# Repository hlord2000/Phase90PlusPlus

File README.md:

# This is a modified and extended Phase90 pedal, intended to fit into a [1590BB enclosure](https://lovemyswitches.com/1590bb-enclosure-bare-aluminum-powder-coat/). Enjoy.

## Interesting features
This pedal uses a software-controlled LFO [(StompLFO, a PIC microcontroller programmed by ElectricDruid)](https://electricdruid.net/product/stomplfo/) to generate a cool bunch of waveforms. The specific waveform is controlled with a potentiometer. An op-amp mixer is included on the output of the pedal, too, so that a musician can alter the mix of wet/dry tone. Finally, the traditional frequency potentiometer is included. This is a true bypass pedal.

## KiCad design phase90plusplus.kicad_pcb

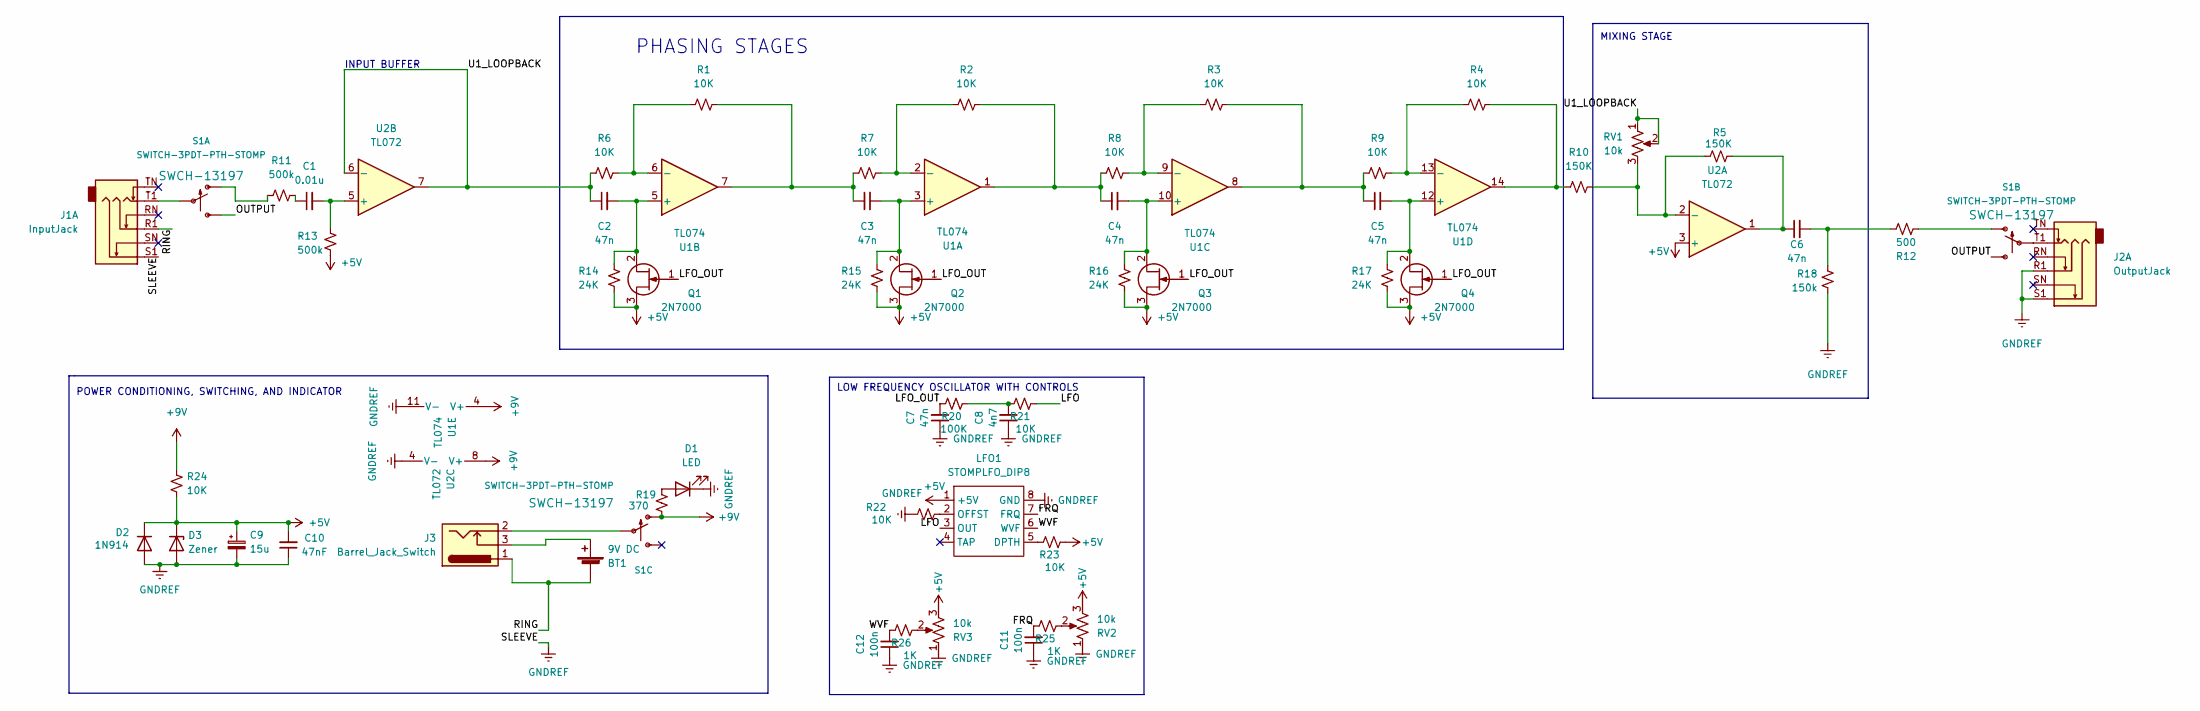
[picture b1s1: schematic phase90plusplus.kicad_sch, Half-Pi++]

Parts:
BT1: 9V DC; JST_EH_S2B-EH_1x02_P2.50mm_Horizontal
C1: 0.01u; C_Disc_D7.5mm_W2.5mm_P5.00mm
C2, C3, C4, C5, C6, C7: 47n; C_Disc_D7.5mm_W2.5mm_P5.00mm
C8: 4n7; C_Disc_D7.5mm_W2.5mm_P5.00mm
C9: 15u; CP_Radial_D4.0mm_P1.50mm
C10: 47nF; C_Disc_D7.5mm_W2.5mm_P5.00mm
C11, C12: 100n; C_Disc_D7.5mm_W2.5mm_P5.00mm
D1: LED; LED_D3.0mm
D2: 1N914; D_DO-35_SOD27_P7.62mm_Horizontal
D3: Zener; D_DO-35_SOD27_P7.62mm_Horizontal
J1: InputJack; Jack_6.35mm_Neutrik_NRJ6HM-1_Horizontal
J2: OutputJack; Jack_6.35mm_Neutrik_NRJ6HM-1_Horizontal
J3: Barrel_Jack_Switch; BarrelJack_Horizontal
LFO1: STOMPLFO_DIP8; DIP-8_W7.62mm_Socket
Q1, Q2, Q3, Q4: 2N7000; TO-92_Inline
R1, R2, R3, R4, R6, R7, R8, R9, R21, R22, R23, R24: 10K; R_Axial_DIN0207_L6.3mm_D2.5mm_P10.16mm_Horizontal
R5, R10: 150K; R_Axial_DIN0207_L6.3mm_D2.5mm_P10.16mm_Horizontal
R11, R13: 500k; R_Axial_DIN0207_L6.3mm_D2.5mm_P10.16mm_Horizontal
R12: 500; R_Axial_DIN0207_L6.3mm_D2.5mm_P10.16mm_Horizontal
R14, R15, R16, R17: 24K; R_Axial_DIN0207_L6.3mm_D2.5mm_P10.16mm_Horizontal
R18: 150k; R_Axial_DIN0207_L6.3mm_D2.5mm_P10.16mm_Horizontal
R19: 370; R_Axial_DIN0207_L6.3mm_D2.5mm_P10.16mm_Horizontal
R20: 100K; R_Axial_DIN0207_L6.3mm_D2.5mm_P10.16mm_Horizontal
R25, R26: 1K; R_Axial_DIN0207_L6.3mm_D2.5mm_P10.16mm_Horizontal
RV1, RV2, RV3: 10k; SolderWire-0.1sqmm_1x03_P3.6mm_D0.4mm_OD1mm_Relief
S1: SWITCH-3PDT-PTH-STOMP; STOMP_SWITCH_3PDT
U1: TL074; DIP-14_W7.62mm
U2: TL072; DIP-8_W7.62mm

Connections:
+5V: C9.1, C10.2, D2.1 (K), D3.1 (K), LFO1.1 (+5V), Q1.3 (D), Q2.3 (D), Q3.3 (D), Q4.3 (D), R13.1, R14.1, R15.1, R16.1, R17.1, R23.1, R24.2, RV2.3, RV3.3, U2.3 (+)
+9V: R19.1, R24.1, S1.P$7 (O), U1.4 (V+), U2.8 (V+)
/FRQ: C11.2, LFO1.7 (FRQ), R25.2
/LFO: LFO1.3 (OUT), R21.1
/LFO_OUT: C7.2, Q1.1 (G), Q2.1 (G), Q3.1 (G), Q4.1 (G), R20.2
/OUTPUT: S1.P$3 (S), S1.P$6 (S)
/RING: BT1.2 (-), J1.R1, J3.1
/U1_LOOPBACK: C2.1, R6.1, RV1.1, RV1.2, U2.6 (-), U2.7
/WVF: C12.2, LFO1.6 (WVF), R26.2
GNDREF: C7.1, C8.1, C9.2, C10.1, C11.1, C12.1, D1.1 (K), D2.2 (A), D3.2 (A), J1.S1, J2.R1, J2.S1, LFO1.8 (GND), R18.1, R22.2, RV2.1, RV3.1, U1.11 (V-), U2.4 (V-)
unnamed: BT1.1 (+), J3.3
unnamed: C1.1, R11.2
unnamed: C1.2, R13.2, U2.5 (+)
unnamed: C2.2, Q1.2 (S), R14.2, U1.5 (+)
unnamed: C3.1, R1.2, R7.1, U1.7
unnamed: C3.2, Q2.2 (S), R15.2, U1.3 (+)
unnamed: C4.1, R2.2, R8.1, U1.1
unnamed: C4.2, Q3.2 (S), R16.2, U1.10 (+)
unnamed: C5.1, R3.2, R9.1, U1.8
unnamed: C5.2, Q4.2 (S), R17.2, U1.12 (+)
unnamed: C6.1, R5.2, U2.1
unnamed: C6.2, R12.2, R18.2
unnamed: C8.2, R20.1, R21.2
unnamed: D1.2 (A), R19.2
unnamed: J1.T1, S1.P$2
unnamed: J2.T1, S1.P$5
unnamed: J3.2, S1.P$8
unnamed: LFO1.2 (OFFST), R22.1
unnamed: LFO1.5 (DPTH), R23.2
unnamed: R1.1, R6.2, U1.6 (-)
unnamed: R2.1, R7.2, U1.2 (-)
unnamed: R3.1, R8.2, U1.9 (-)
unnamed: R4.1, R9.2, U1.13 (-)
unnamed: R4.2, R10.1, U1.14
unnamed: R5.1, R10.2, RV1.3, U2.2 (-)
unnamed: R11.1, S1.P$1 (O)
unnamed: R12.1, S1.P$4 (O)
unnamed: R25.1, RV2.2
unnamed: R26.1, RV3.2

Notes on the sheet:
INPUT BUFFER
POWER CONDITIONING, SWITCHING, AND INDICATOR
LOW FREQUENCY OSCILLATOR WITH CONTROLS
MIXING STAGE
PHASING STAGES

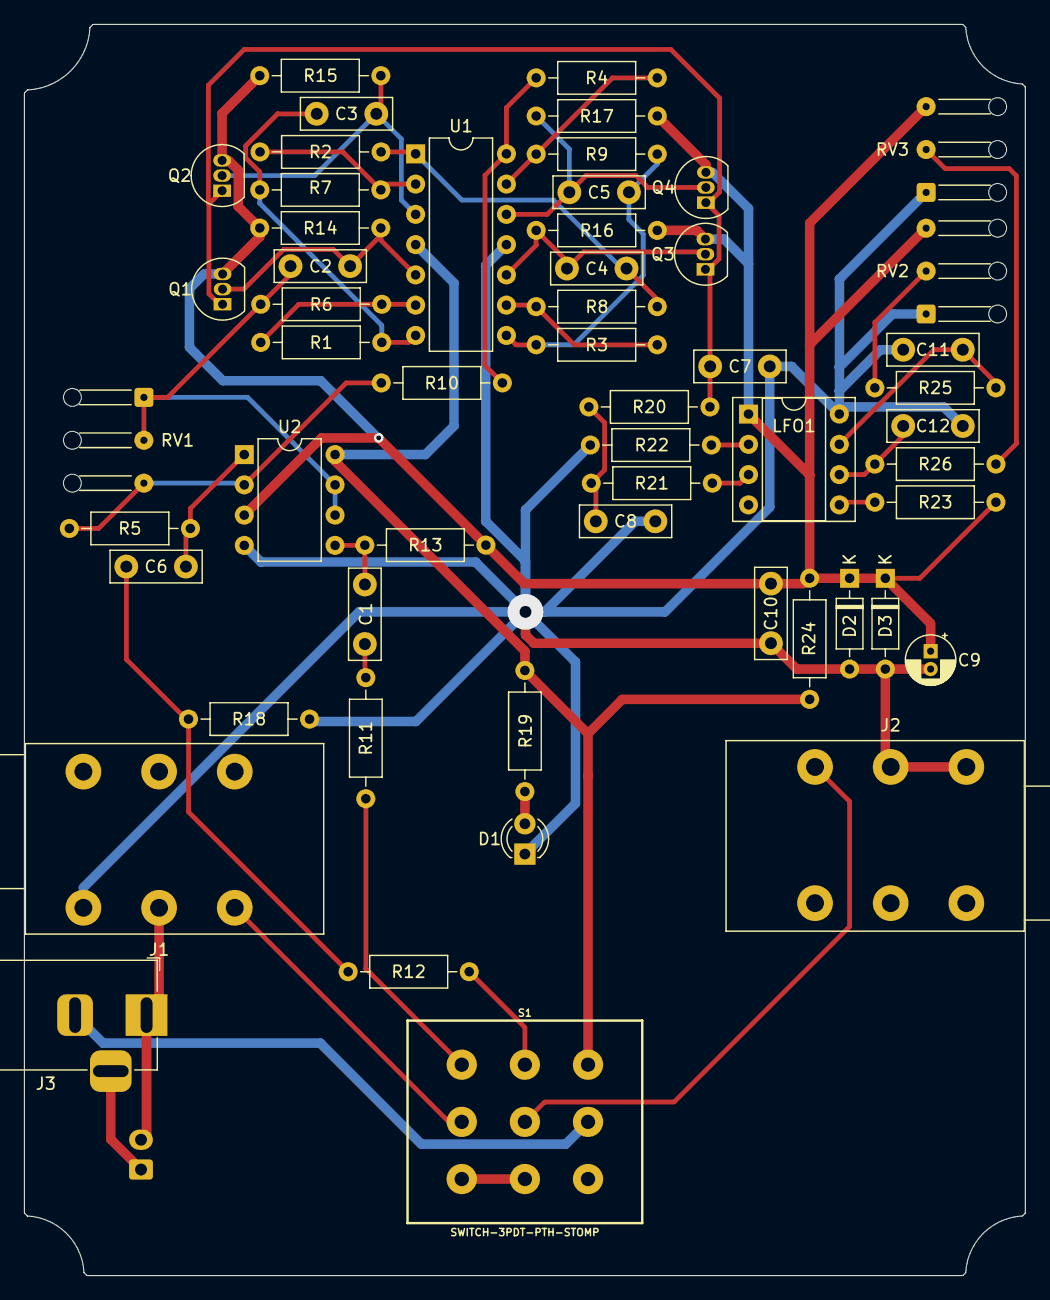
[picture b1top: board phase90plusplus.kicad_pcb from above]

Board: 2 copper layers, 84.0 x 105.0 mm, 56 parts (1 on the bottom side), 39 nets.

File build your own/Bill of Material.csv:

"Source:","C:\Users\Helmut Lord\Documents\Phase90++\phase90plusplus.kicad_sch"
"Date:","5/4/2022 3:37:26 PM"
"Tool:","Eeschema (6.0.1)"
"Generator:","C:\Program Files\KiCad\6.0\bin\scripting\plugins/bom_csv_grouped_by_value_with_fp.py"
"Component Count:","56"
"Ref","Qnty","Value","Cmp name","Footprint","Description","Vendor"
"BT1, ","1","9V DC","Battery_Cell","Connector_JST:JST_EH_S2B-EH_1x02_P2.50mm_Horizontal","Single-cell battery",""
"C1, ","1","0.01u","C_Small","Capacitor_THT:C_Disc_D7.5mm_W2.5mm_P5.00mm","Unpolarized capacitor, small symbol",""
"C2, C3, C4, C5, C6, C7, ","6","47n","C_Small","Capacitor_THT:C_Disc_D7.5mm_W2.5mm_P5.00mm","Unpolarized capacitor, small symbol",""
"C8, ","1","4n7","C_Small","Capacitor_THT:C_Disc_D7.5mm_W2.5mm_P5.00mm","Unpolarized capacitor, small symbol",""
"C9, ","1","15u","C_Polarized_Small","Capacitor_THT:CP_Radial_D4.0mm_P1.50mm","Polarized capacitor, small symbol",""
"C10, ","1","47nF","C_Small","Capacitor_THT:C_Disc_D7.5mm_W2.5mm_P5.00mm","Unpolarized capacitor, small symbol",""
"C11, C12, ","2","100n","C_Small","Capacitor_THT:C_Disc_D7.5mm_W2.5mm_P5.00mm","Unpolarized capacitor, small symbol",""
"D1, ","1","LED","LED","LED_THT:LED_D3.0mm","Light emitting diode",""
"D2, ","1","1N914","1N914","Diode_THT:D_DO-35_SOD27_P7.62mm_Horizontal","100V 0.3A Small Signal Fast Switching Diode, DO-35",""
"D3, ","1","Zener","D_Zener","Diode_THT:D_DO-35_SOD27_P7.62mm_Horizontal","Zener diode",""
"J1, ","1","InputJack","AudioJack3_Dual_Switch_1","Connector_Audio:Jack_6.35mm_Neutrik_NRJ6HM-1_Horizontal","Audio Jack, Dual, 3 Poles (Stereo / TRS), Switched Poles (Normalling)",""
"J2, ","1","OutputJack","AudioJack3_Dual_Switch","Connector_Audio:Jack_6.35mm_Neutrik_NRJ6HM-1_Horizontal","Audio Jack, Dual, 3 Poles (Stereo / TRS), Switched Poles (Normalling)",""
"J3, ","1","Barrel_Jack_Switch","Barrel_Jack_Switch","Connector_BarrelJack:BarrelJack_Horizontal","DC Barrel Jack with an internal switch",""
"LFO1, ","1","STOMPLFO_DIP8","STOMPLFO_DIP8","Package_DIP:DIP-8_W7.62mm_Socket","",""
"Q1, Q2, Q3, Q4, ","4","2N7000","BF245A","Package_TO_SOT_THT:TO-92_Inline","50mA Id, 30V Vgs, N-Channel FET Transistor, TO-92",""
"R1, R2, R3, R4, R6, R7, R8, R9, R21, R22, R23, R24, ","12","10K","R_Small_US","Resistor_THT:R_Axial_DIN0207_L6.3mm_D2.5mm_P10.16mm_Horizontal","Resistor, small US symbol",""
"R5, R10, ","2","150K","R_Small_US","Resistor_THT:R_Axial_DIN0207_L6.3mm_D2.5mm_P10.16mm_Horizontal","Resistor, small US symbol",""
"R11, R13, ","2","500k","R_Small_US","Resistor_THT:R_Axial_DIN0207_L6.3mm_D2.5mm_P10.16mm_Horizontal","Resistor, small US symbol",""
"R12, ","1","500","R_Small_US","Resistor_THT:R_Axial_DIN0207_L6.3mm_D2.5mm_P10.16mm_Horizontal","Resistor, small US symbol",""
"R14, R15, R16, R17, ","4","24K","R_Small_US","Resistor_THT:R_Axial_DIN0207_L6.3mm_D2.5mm_P10.16mm_Horizontal","Resistor, small US symbol",""
"R18, ","1","150k","R_Small_US","Resistor_THT:R_Axial_DIN0207_L6.3mm_D2.5mm_P10.16mm_Horizontal","Resistor, small US symbol",""
"R19, ","1","370","R_Small_US","Resistor_THT:R_Axial_DIN0207_L6.3mm_D2.5mm_P10.16mm_Horizontal","Resistor, small US symbol",""
"R20, ","1","100K","R_Small_US","Resistor_THT:R_Axial_DIN0207_L6.3mm_D2.5mm_P10.16mm_Horizontal","Resistor, small US symbol",""
"R25, R26, ","2","1K","R_Small_US","Resistor_THT:R_Axial_DIN0207_L6.3mm_D2.5mm_P10.16mm_Horizontal","Resistor, small US symbol",""
"RV1, RV2, RV3, ","3","10k","R_Potentiometer_US","Connector_Wire:SolderWire-0.1sqmm_1x03_P3.6mm_D0.4mm_OD1mm_Relief","Potentiometer, US symbol",""
"S1, ","1","SWITCH-3PDT-PTH-STOMP","SWITCH-3PDT-PTH-STOMP","Switches:STOMP_SWITCH_3PDT","3-Pole, Double-Throw (3PDT) Switch Three-pole, double-throw stomp switch. Drawn as three separate gates for schematic clarity. <h4>SparkFun Products</h4><ul><li>Used in <a href=""https://www.sparkfun.com/products/13124"">SparkFun Proto Pedal</a> (PRT-13124)</li></ul>",""
"U1, ","1","TL074","TL074","Package_DIP:DIP-14_W7.62mm","Quad Low-Noise JFET-Input Operational Amplifiers, DIP-14/SOIC-14",""
"U2, ","1","TL072","TL072","Package_DIP:DIP-8_W7.62mm","Dual Low-Noise JFET-Input Operational Amplifiers, DIP-8/SOIC-8",""

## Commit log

2022-03-31 Initial commit.
2022-03-31 Added README
2022-03-31 update gitingore
2022-03-31 update gitignore
2022-03-31 Initial revision of schematic.
2022-04-08 Hardware commit.
2022-04-29 Added libraries, initial routing and layout started. Schematic revised to add LED and power handling.
2022-05-04 Revision 1.0 complete.
